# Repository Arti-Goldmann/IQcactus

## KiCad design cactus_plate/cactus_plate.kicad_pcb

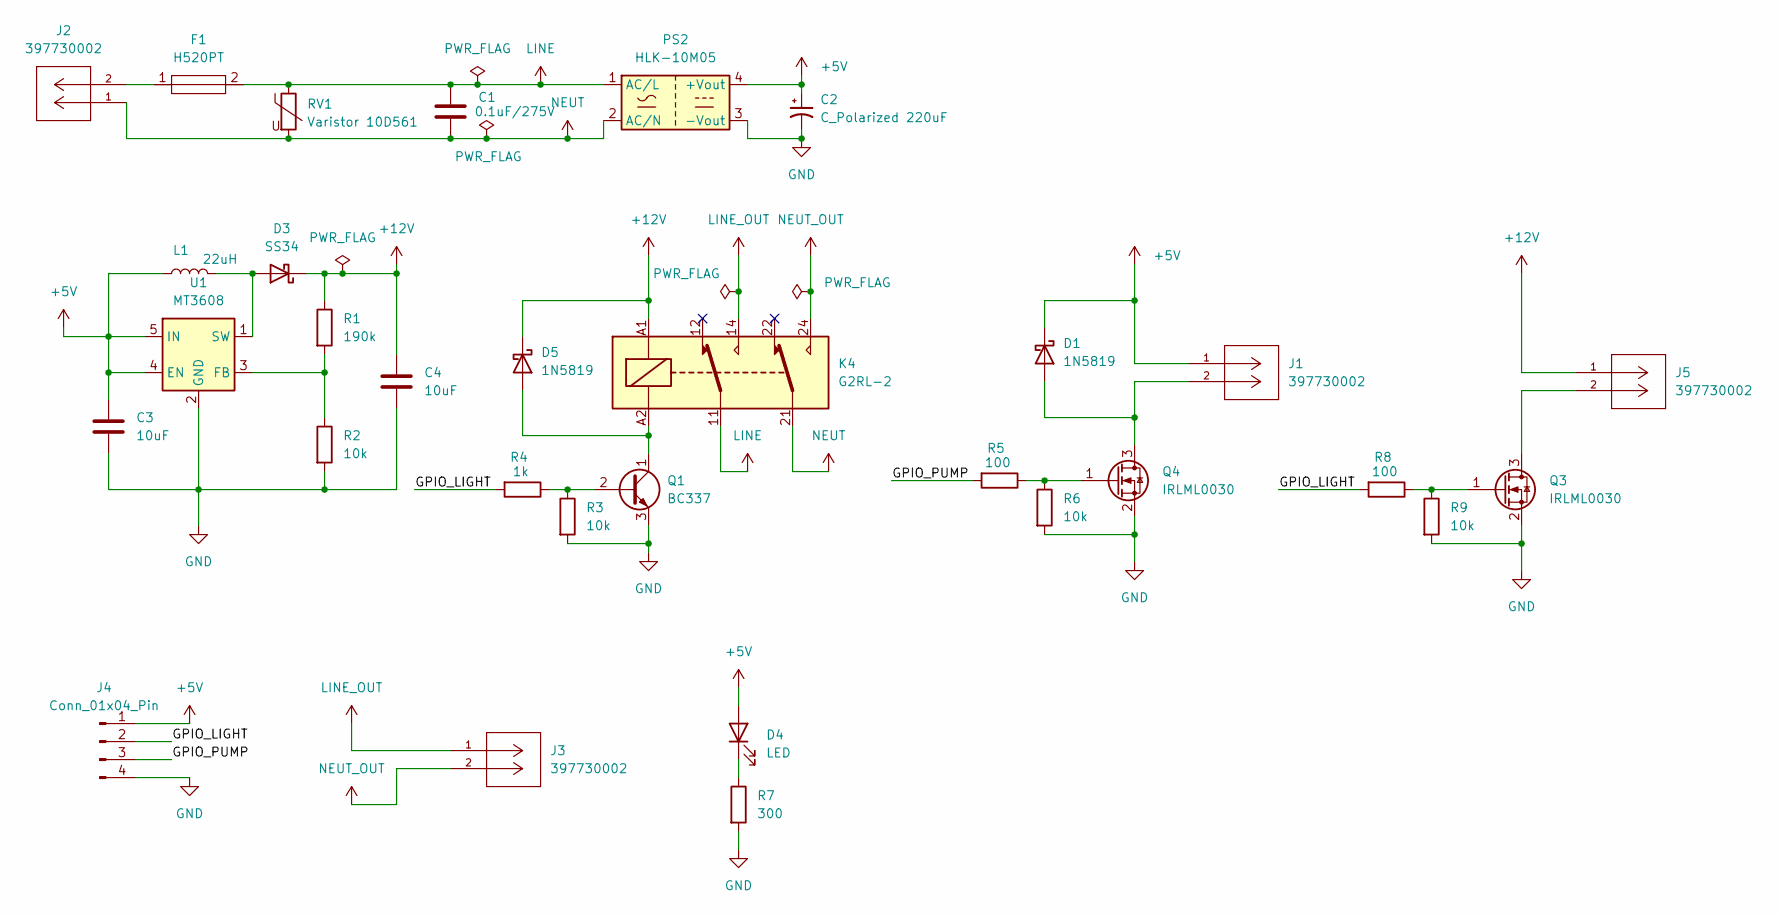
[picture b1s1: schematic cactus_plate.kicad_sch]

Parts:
C1: 0.1uF/275V; C_Axial_L12.0mm_D6.5mm_P15.00mm_Horizontal
C2: C_Polarized 220uF; CP_Radial_D10.0mm_P3.50mm
C3, C4: 10uF; C_0805_2012Metric_Pad1.18x1.45mm_HandSolder
D1, D5: 1N5819; D_DO-41_SOD81_P10.16mm_Horizontal
D3: SS34; D_SMA
D4: LED; R_0805_2012Metric_Pad1.20x1.40mm_HandSolder
F1: H520PT
J1, J2, J3, J5: 397730002; PhoenixContact_MCV_1,5_2-G-5.08_1x02_P5.08mm_Vertical; MANUFACTURER_PART_NUMBER 397730002
J4: Conn_01x04_Pin; PinHeader_1x04_P2.54mm_Vertical
K4: G2RL-2; Relay_DPDT_Omron_G2RL-2
L1: 22uH; L_10.4x10.4_H4.8
PS2: HLK-10M05; Converter_ACDC_Hi-Link_HLK-10Mxx
Q1: BC337; TO-92_Inline
Q3, Q4: IRLML0030; SOT-23
R1: 190k; R_0805_2012Metric_Pad1.20x1.40mm_HandSolder
R2, R3, R6, R9: 10k; R_0805_2012Metric_Pad1.20x1.40mm_HandSolder
R4: 1k; R_0805_2012Metric_Pad1.20x1.40mm_HandSolder
R5, R8: 100; R_0805_2012Metric_Pad1.20x1.40mm_HandSolder
R7: 300; R_0805_2012Metric_Pad1.20x1.40mm_HandSolder
RV1: Varistor 10D561; RV_Disc_D12mm_W5.8mm_P7.5mm
U1: MT3608; SOT-23-6

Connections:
+5V: C2.1, C3.1, D1.1 (K), D4.2 (A), J1.1, J4.1, L1.1, PS2.4 (+Vout), U1.4 (EN), U1.5 (IN)
+12V: C4.1, D3.1 (K), D5.1 (K), J5.1, K4.A1, R1.1
/GPIO_LIGHT: J4.2, R4.2, R8.2
/GPIO_PUMP: J4.3, R5.2
GND: C2.2, C3.2, C4.2, J4.4, PS2.3 (-Vout), Q1.3 (E), Q3.2 (S), Q4.2 (S), R2.2, R3.2, R6.2, R7.2, R9.2, U1.2 (GND)
LINE: C1.1, F1.2, K4.11, PS2.1 (AC/L), RV1.1
LINE_OUT: J3.1, K4.14
NEUT: C1.2, J2.1, K4.21, PS2.2 (AC/N), RV1.2
NEUT_OUT: J3.2, K4.24
unnamed: D1.2 (A), J1.2, Q4.3 (D)
unnamed: D3.2 (A), L1.2, U1.1 (SW)
unnamed: D4.1 (K), R7.1
unnamed: D5.2 (A), K4.A2, Q1.1 (C)
unnamed: F1.1, J2.2
unnamed: Q1.2 (B), R3.1, R4.1
unnamed: J5.2, Q3.3 (D)
unnamed: Q3.1 (G), R8.1, R9.1
unnamed: Q4.1 (G), R5.1, R6.1
unnamed: R1.2, R2.1, U1.3 (FB)

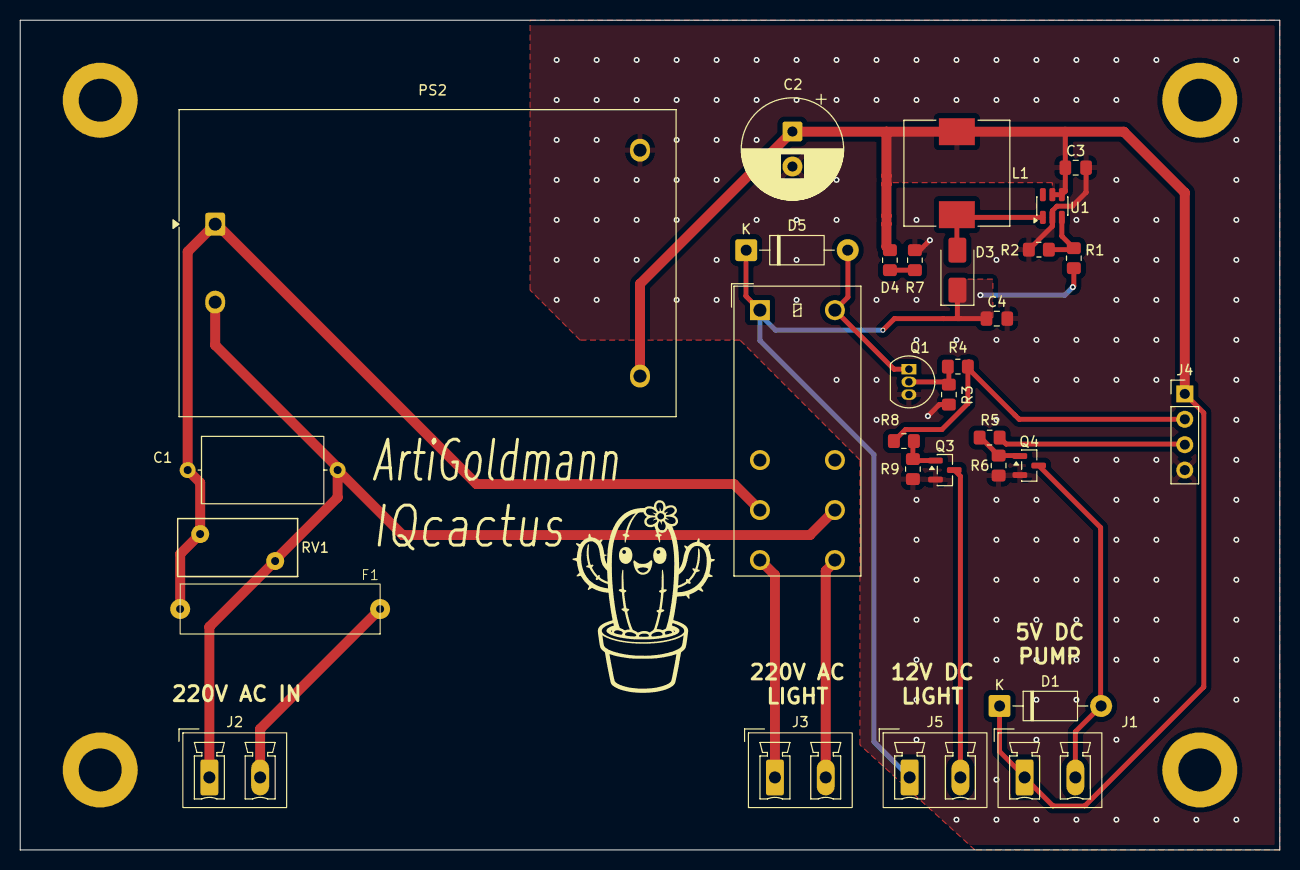
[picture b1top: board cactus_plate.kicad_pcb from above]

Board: 2 copper layers, 126.0 x 83.0 mm, 31 parts (0 on the bottom side), 19 nets.

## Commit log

2026-03-21 Версия без подсветки
2026-03-22 Переделал плату, добавил разъем для подсветки
2026-04-19 сделал 3d модель корпуса
2026-05-24 начал делать софт для m5stick
2026-05-24 устанановил соединение с сервером
2026-05-24 полинг сервера каждую секунду
2026-05-24 фикс дисплея
2026-05-24 spi через прерывания, а не через dma, а то дисплей подвисал
